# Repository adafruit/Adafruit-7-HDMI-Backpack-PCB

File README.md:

## Adafruit 7" HDMI Backpack PCB
&nbsp; <br />
Click to purchase from the Adafruit Shop:
- [HDMI 7" 800x480 Display Backpack - Without Touch](https://www.adafruit.com/product/2406)
- [HDMI 7" 800x480 Display Backpack - With Touchscreen](https://www.adafruit.com/product/2407)

Its a mini panel-mountable HDMI monitor! So small and simple, you can use this display with any computer that has HDMI output, and the shape makes it easy to attach to a case or rail. This backpack features the TFP401 for decoding video, and includes the attached display so its plug-n-play.

The TFP401 is a beefy DVI/HDMI decoder from TI. It can take unencrypted video and pipe out the raw 24-bit color pixel data - HDCP not supported! The 7" display is 800x480 resolution, which is just enough to run most software, but still small enough that it can be used in portable or embedded projects without the bulk.

You can even power the entire display from a USB port. With the default 7" 800x480 display and 150mA backlight current, the current draw is 600mA total. You can reduce that down 400mA by running the backlight at half-brightness (75mA). With the backlight off, the decoder and display itself draws 250mA. If you want more backlight control, there's a PWM input, connect that to your microcontroller or other PWM output and you can continuously dim the backlight as desired.

We have two versions, one is video only and one is video+touch.

For more details, check out the product pages at

- https://www.adafruit.com/product/2406
- https://www.adafruit.com/product/2407

PCB files for the Adafruit 7" HDMI Backpack. The format is EagleCAD schematic and board layout

### License

Adafruit invests time and resources providing this open source design, please support Adafruit and open-source hardware by purchasing products from [Adafruit](https://www.adafruit.com)!

All text above must be included in any redistribution

Designed by Limor Fried/Ladyada for Adafruit Industries.
Creative Commons Attribution/Share-Alike, all text above must be included in any redistribution. 
See license.txt for additional information.

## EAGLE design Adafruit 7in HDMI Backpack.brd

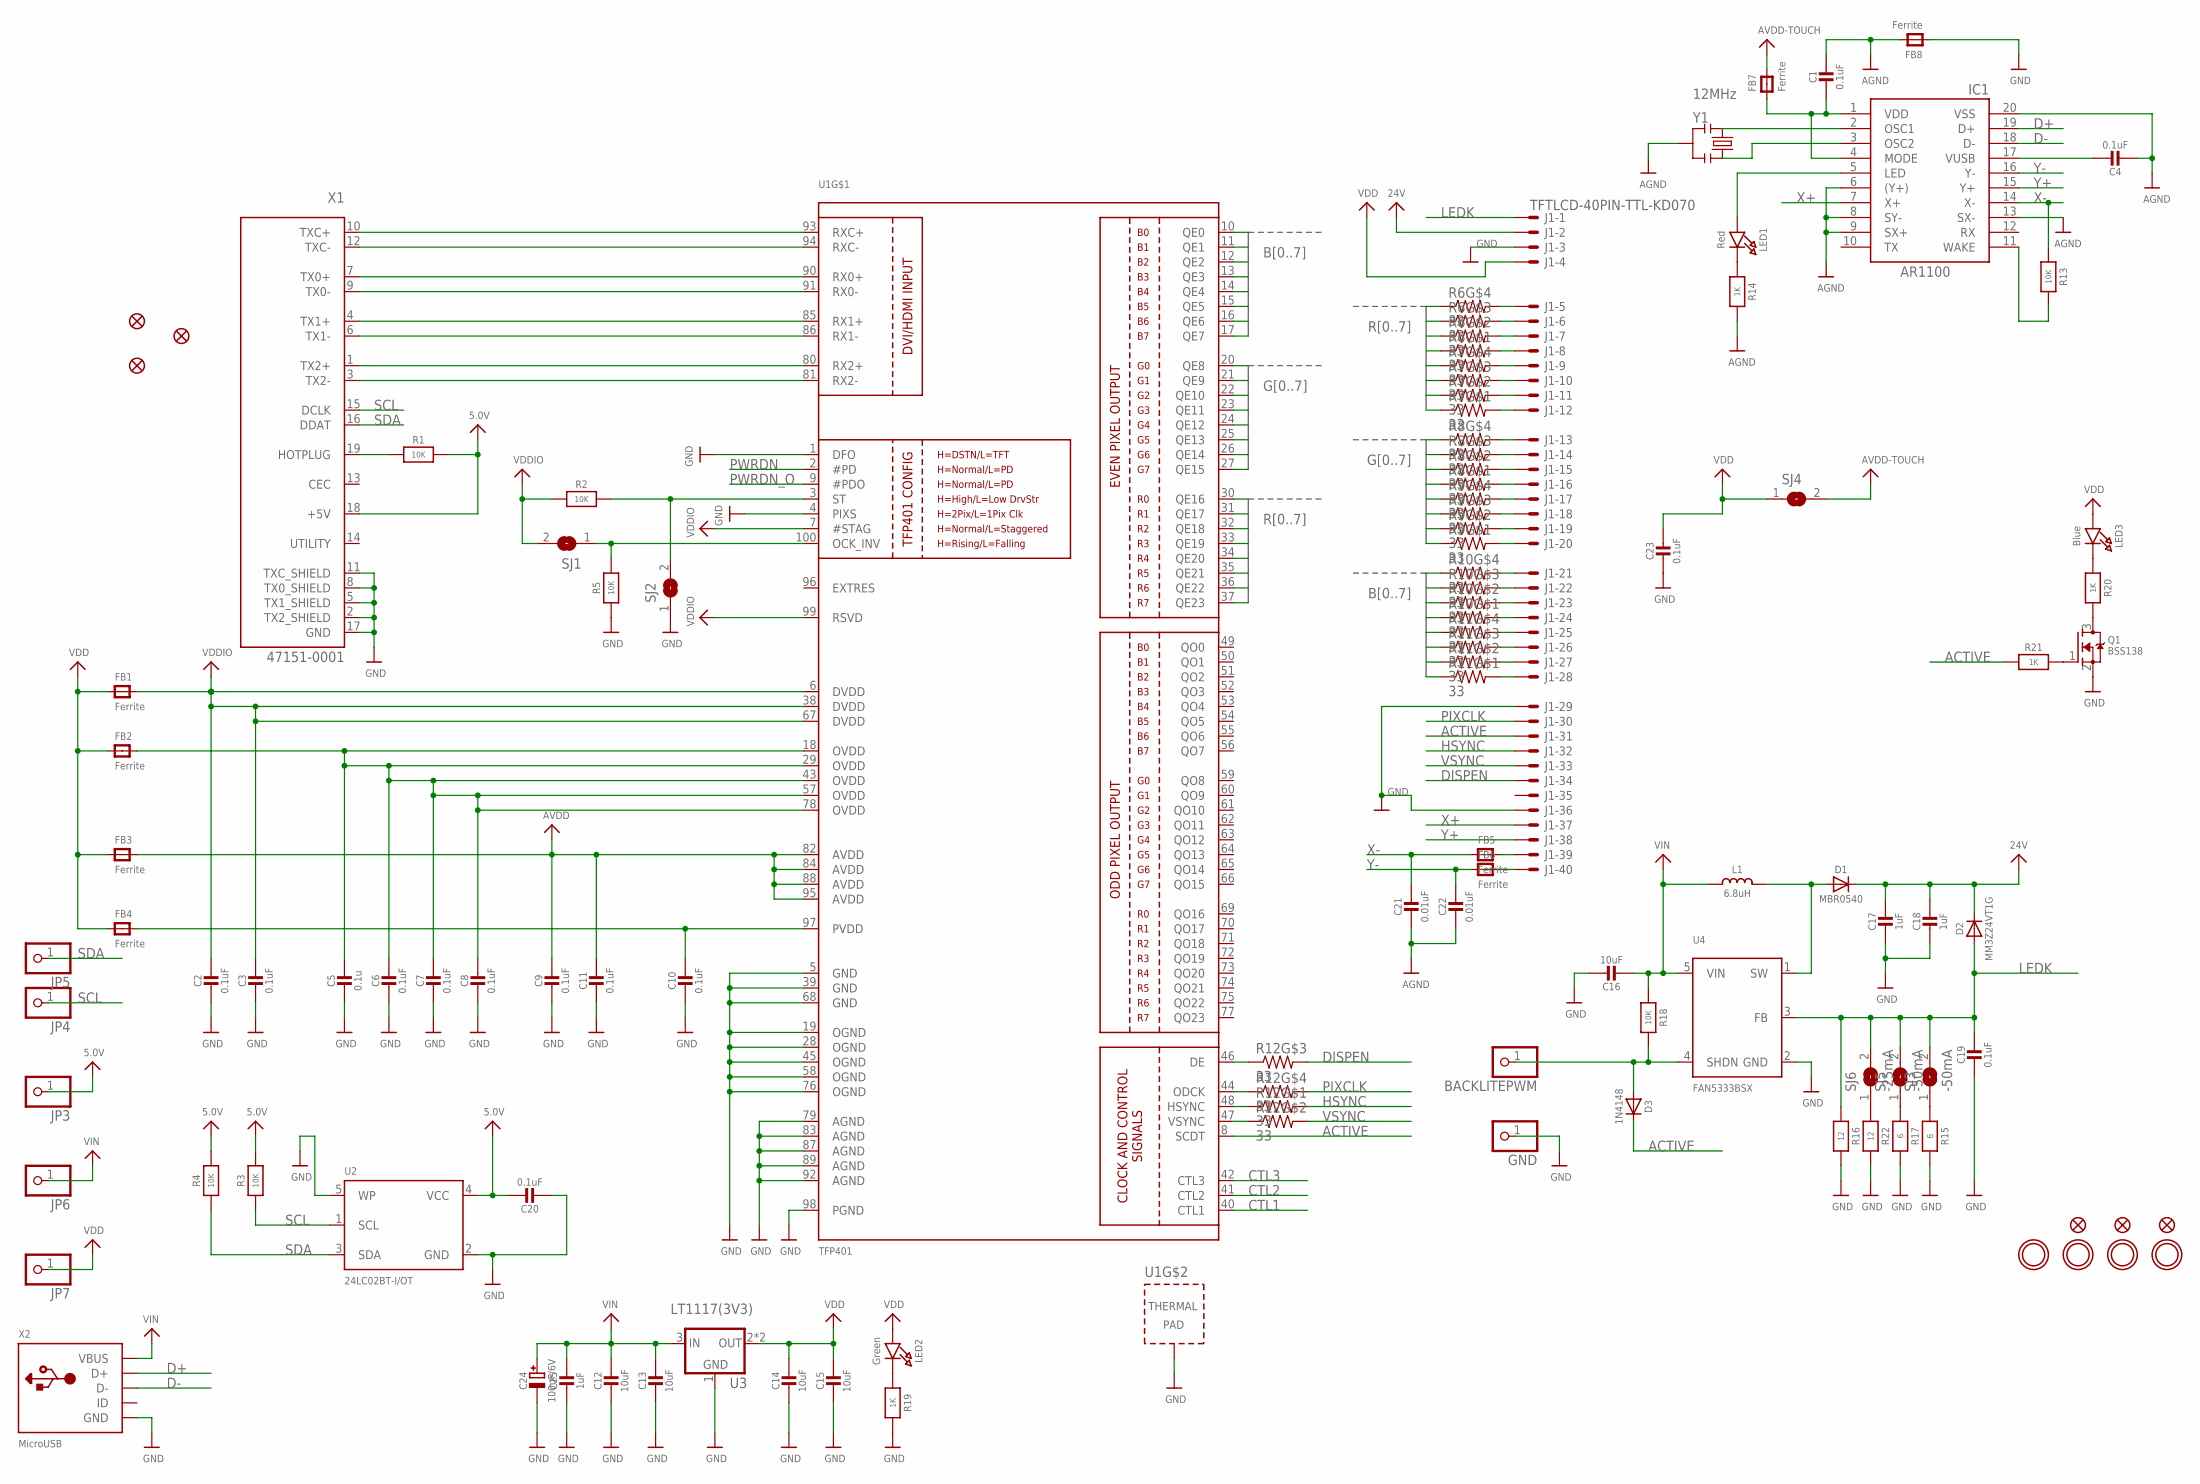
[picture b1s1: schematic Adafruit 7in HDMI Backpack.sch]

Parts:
BACKLITEPWM: HEADER-1X1-SMD_MASKHELD_2X2MM; 1X01_SMD_MASKHELD_2X2MM
C1, C2, C3, C7, C8, C9, C10, C11, C19, C20, C23: 0.1uF; 0805-NO
C4, C6: 0.1uF; _0805MP
C5: 0.1u; 0805-NO
C12, C13, C14, C15, C16: 10uF; 0805-NO
C17, C18, C25: 1uF; 0805-NO
C21, C22: 0.01uF; 0805-NO
C24: 100uF/6V; PANASONIC_C
D1: MBR0540; SOD-123
D2: MM3Z24VT1G; SMADIODE
D3: 1N4148; SOD-323
FB1, FB2, FB3, FB4, FB5, FB6, FB7, FB8: Ferrite; _0805MP
FID1, FID2, FID3, FID4, FID5, FID6: FIDUCIAL""; FIDUCIAL_1MM
GND: HEADER-1X1-SMD_MASKHELD_2X2MM; 1X01_SMD_MASKHELD_2X2MM
IC1: AR1100; TSSOP20-5.3MMBODY
J1: TFTLCD-40PIN-TTL-KD070; TFTLCD-KD070GD21-40NT
JP3, JP4, JP5, JP6, JP7: HEADER-1X1-SMD_MASKHELD_2X2MM; 1X01_SMD_MASKHELD_2X2MM
L1: 6.8uH; INDUCTOR_5X5MM_NR5040_NOTHERMALS
LED1: Red; CHIPLED_0805_NOOUTLINE
LED2: Green; CHIPLED_0805_NOOUTLINE
LED3: Blue; CHIPLED_0805_NOOUTLINE
Q1: BSS138; SOT23-WIDE
R1, R3, R4, R13, R18: 10K; 0805-NO
R2, R5: 10K; _0805MP
R6, R7, R8, R9, R10, R11, R12: 33; RESPACK_4X0603
R14, R19, R20, R21: 1K; 0805-NO
R15, R17: 6; 0805-NO
R16, R22: 12; 0805-NO
SJ1, SJ2: SOLDERJUMPER; SOLDERJUMPER_ARROW_NOPASTE
SJ3, SJ5: -50mA; SOLDERJUMPER_CLOSEDWIRE
SJ4: SOLDERJUMPERCLOSED; SOLDERJUMPER_CLOSEDWIRE
SJ6: -25mA; SOLDERJUMPER_CLOSEDWIRE
U1: TFP401; S-PQFP-G100
U2: 24LC02BT-I/OT; SOT23-5
U3: LT1117(3V3); SOT223-R
U4: FAN5333BSX; SOT23-5
U$31, U$32, U$33, U$34: MOUNTINGHOLE3.0; MOUNTINGHOLE_3.0_PLATED
X1: 47151-0001; HDMI_MOLEX_47151-0001_DIMLAYER
X2: MicroUSB; 4UCONN_20329
Y1: 12MHz; RESONATOR-SMD

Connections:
5.0V: C20.1, JP3.1, R1.2, R3.2, R4.2, U2.4 (VCC), X1.18 (+5V)
24V: C17.1, C18.1, D1.C, D2.C, J1.2 (MS)
ACTIVE: D3.C, J1.31 (MS), R21.1, U1.8 (SCDT)
AGND: C1.1, C4.2, C21.2, C22.2, FB8.2, IC1.6 ((Y+)), IC1.8 (SY-), IC1.9 (SX+), IC1.13 (SX-), IC1.20 (VSS), R14.2, Y1.2
ASD: R12.3 (1), U1.46 (DE)
AVDD: C9.1, C11.1, FB3.2, U1.82 (AVDD), U1.84 (AVDD), U1.88 (AVDD), U1.95 (AVDD)
AVDD2: FB7.2, SJ4.2
B0: R10.4 (1), U1.10 (QE0)
B1: R10.3 (1), U1.11 (QE1)
B2: R10.2 (1), U1.12 (QE2)
B3: R10.1, U1.13 (QE3)
B4: R11.4 (1), U1.14 (QE4)
B5: R11.3 (1), U1.15 (QE5)
B6: R11.2 (1), U1.16 (QE6)
B7: R11.1, U1.17 (QE7)
CTL1: U1.40 (CTL1)
CTL2: U1.41 (CTL2)
CTL3: U1.42 (CTL3)
CVB: R12.2 (1), U1.47 (VSYNC)
D+: IC1.19 (D+), X2.D+
D-: IC1.18 (D-), X2.D-
DISPEN: J1.34 (MS), R12.6 (2)
G0: R8.4 (1), U1.20 (QE8)
G1: R8.3 (1), U1.21 (QE9)
G2: R8.2 (1), U1.22 (QE10)
G3: R8.1, U1.23 (QE11)
G4: R9.4 (1), U1.24 (QE12)
G5: R9.3 (1), U1.25 (QE13)
G6: R9.2 (1), U1.26 (QE14)
G7: R9.1, U1.27 (QE15)
GND: C2.2, C3.2, C5.2, C6.2, C7.2, C8.2, C9.2, C10.2, C11.2, C12.2, C13.2, C14.2, C15.2, C16.1, C17.2, C18.2, C19.2, C20.2, C23.2, C24.-, C25.2, FB8.1, GND.1, J1.3 (MS), J1.29 (MS), J1.36 (MS), Q1.2 (S), R5.1, R15.2, R16.2, R17.2, R19.2, R22.2, SJ2.1, U1.1 (DFO), U1.4 (PIXS), U1.5 (GND), U1.19 (OGND), U1.28 (OGND), U1.39 (GND), U1.45 (OGND), U1.58 (OGND), U1.68 (GND), U1.76 (OGND), U1.79 (AGND), U1.83 (AGND), U1.87 (AGND), U1.89 (AGND), U1.92 (AGND), U1.98 (PGND), U1.P$1 (TP), U1.P$2 (TP), U1.P$3 (TP), U1.P$4 (TP), U1.P$5 (TP), U1.P$6 (TP), U1.P$7 (TP), U1.P$8 (TP), U1.P$9 (TP), U1.P$10 (TP), U1.P$11 (TP), U1.P$12 (TP), U1.P$13 (TP), U1.P$14 (TP), U1.P$15 (TP), U1.P$16 (TP), U1.THERMAL (TP), U2.2 (GND), U2.5 (WP), U3.1 (GND), U4.2 (GND), X1.2 (TX2_SHIELD), X1.5 (TX1_SHIELD), X1.8 (TX0_SHIELD), X1.11 (TXC_SHIELD), X1.17 (GND), X1.P$1 (GND), X1.P$2 (GND), X1.P$3 (GND), X1.P$4 (GND), X2.BASE@1 (GND), X2.BASE@2 (GND), X2.GND, X2.SPRT@1 (GND), X2.SPRT@2 (GND), X2.SPRT@3 (GND), X2.SPRT@4 (GND)
HSYNC: J1.32 (MS), R12.8 (2)
LEDK: C19.1, D2.A, J1.1 (MSV), R16.1, SJ3.2, SJ5.2, SJ6.2, U4.3 (FB)
unnamed: U1.93 (RXC+), X1.10 (TXC+)
unnamed: U1.94 (RXC-), X1.12 (TXC-)
unnamed: U1.90 (RX0+), X1.7 (TX0+)
unnamed: U1.91 (RX0-), X1.9 (TX0-)
unnamed: U1.85 (RX1+), X1.4 (TX1+)
unnamed: U1.86 (RX1-), X1.6 (TX1-)
unnamed: U1.80 (RX2+), X1.1 (TX2+)
unnamed: U1.81 (RX2-), X1.3 (TX2-)
unnamed: R1.1, X1.19 (HOTPLUG)
unnamed: IC1.2 (OSC1), Y1.1
unnamed: IC1.3 (OSC2), Y1.3
unnamed: C4.1, IC1.17 (VUSB)
unnamed: LED2.C, R19.1
unnamed: J1.5 (MS), R6.5 (2)
unnamed: J1.6 (MS), R6.6 (2)
unnamed: J1.7 (MS), R6.7 (2)
unnamed: J1.8 (MS), R6.8 (2)
unnamed: J1.9 (MS), R7.5 (2)
unnamed: J1.10 (MS), R7.6 (2)
unnamed: J1.11 (MS), R7.7 (2)
unnamed: J1.12 (MS), R7.8 (2)
unnamed: J1.13 (MS), R8.5 (2)
unnamed: J1.14 (MS), R8.6 (2)
unnamed: J1.15 (MS), R8.7 (2)
unnamed: J1.16 (MS), R8.8 (2)
unnamed: J1.17 (MS), R9.5 (2)
unnamed: J1.18 (MS), R9.6 (2)
unnamed: J1.19 (MS), R9.7 (2)
unnamed: J1.20 (MS), R9.8 (2)
unnamed: J1.21 (MS), R10.5 (2)
unnamed: J1.22 (MS), R10.6 (2)
unnamed: J1.23 (MS), R10.7 (2)
unnamed: J1.24 (MS), R10.8 (2)
unnamed: J1.25 (MS), R11.5 (2)
unnamed: J1.26 (MS), R11.6 (2)
unnamed: J1.27 (MS), R11.7 (2)
unnamed: R17.1, SJ5.1
unnamed: C10.1, FB4.2, U1.97 (PVDD)
unnamed: J1.28 (MS), R11.8 (2)
unnamed: IC1.11 (WAKE), R13.2
unnamed: LED1.C, R14.1
unnamed: C5.1, C6.1, C7.1, C8.1, FB2.2, U1.18 (OVDD), U1.29 (OVDD), U1.43 (OVDD), U1.57 (OVDD), U1.78 (OVDD)
unnamed: IC1.5 (LED), LED1.A
unnamed: R22.1, SJ6.1
unnamed: LED3.C, R20.1
unnamed: Q1.3 (D), R20.2
unnamed: D1.A, L1.P$2 (2), U4.1 (SW)
unnamed: Q1.1 (G), R21.2
unnamed: R15.1, SJ3.1
unnamed: BACKLITEPWM.1, D3.A, R18.2, U4.4 (SHDN)
unnamed: FB5.2, J1.39 (MS)
unnamed: FB6.2, J1.40 (MS)
unnamed: C1.2, FB7.1, IC1.1 (VDD), IC1.4 (MODE)
OCK_INV: R5.2, SJ1.1, U1.100 (OCK_INV)
PIXCLK: J1.30 (MS), R12.5 (2)
PWRDN: U1.2 (#PD)
PWRDN_O: U1.9 (#PDO)
R0: R6.4 (1), U1.30 (QE16)
R1: R6.3 (1), U1.31 (QE17)
R2: R6.2 (1), U1.32 (QE18)
R3: R6.1, U1.33 (QE19)
R4: R7.4 (1), U1.34 (QE20)
R5: R7.3 (1), U1.35 (QE21)
R6: R7.2 (1), U1.36 (QE22)
R7: R7.1, U1.37 (QE23)
SCL: JP4.1, R3.1, U2.1 (SCL), X1.15 (DCLK)
SDA: JP5.1, R4.1, U2.3 (SDA), X1.16 (DDAT)
ST: R2.2, SJ2.2, U1.3 (ST)
VDD: C14.1, C15.1, C23.1, FB1.1, FB2.1, FB3.1, FB4.1, J1.4 (MS), JP7.1, LED2.A, LED3.A, SJ4.1, U3.2 (OUT), U3.4 (OUT)
VDDIO: C2.1, C3.1, FB1.2, R2.1, SJ1.2, U1.6 (DVDD), U1.7 (#STAG), U1.38 (DVDD), U1.67 (DVDD), U1.99 (RSVD)
VIN: C12.1, C13.1, C16.2, C24.+, C25.1, JP6.1, L1.P$1 (1), R18.1, U3.3 (IN), U4.5 (VIN), X2.VBUS
VSYNC: J1.33 (MS), R12.7 (2)
X+: IC1.7 (X+), J1.37 (MS)
X-: C21.1, FB5.1, IC1.14 (X-), R13.1
XCV: R12.1, U1.48 (HSYNC)
Y+: IC1.15 (Y+), J1.38 (MS)
Y-: C22.1, FB6.1, IC1.16 (Y-)
ZXC: R12.4 (1), U1.44 (ODCK)

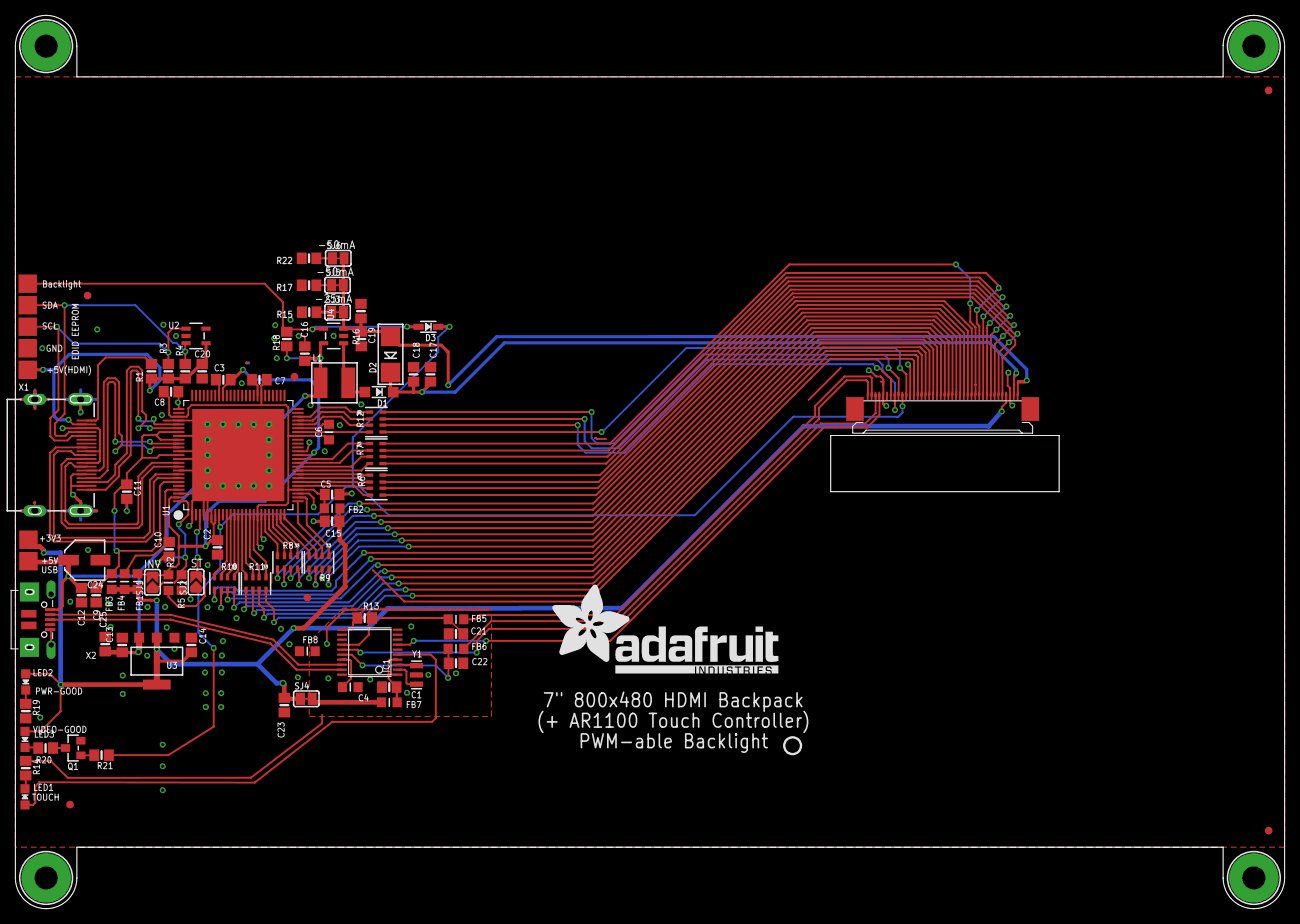
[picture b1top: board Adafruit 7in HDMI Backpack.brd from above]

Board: 2 copper layers, 165.1 x 116.2 mm, 97 parts (1 on the bottom side), 106 nets.

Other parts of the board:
U$75: ADAFRUIT_TEXT_30MM
U$76: PCBFEAT-REV-056

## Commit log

2016-07-25 initzy

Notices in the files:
parts and their libraries:
microbuilder: This work is placed in the public domain, and may be freely used for commercial and non-commercial work with the following conditions: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
SparkFun: Licensing: CC v3.0 Share-Alike You are welcome to use this library for commercial purposes.
